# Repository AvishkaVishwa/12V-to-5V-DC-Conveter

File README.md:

# 12V to 5V DC Converter

## Overview
This project is a 12V to 5V DC-DC buck converter PCB design created with KiCad. The converter allows you to efficiently step down 12V DC power sources to 5V for powering various electronic devices and circuits.

## Features
- Input voltage: 12V DC
- Output voltage: 5V DC
- Buck converter topology for efficient power conversion
- Compact PCB design
- Ready for production

## Directory Structure
- `fabrication-toolkit-options.json` - Configuration for fabrication toolkit
- `PCB design Course.kicad_pcb` - KiCad PCB layout file
- `PCB design Course.kicad_sch` - KiCad schematic file
- `PCB design Course.kicad_pro` - KiCad project file
- `database/` - Project database files
- `PCB design Course-backups/` - Automatic backup files
- `production/` - Manufacturing files (Gerbers, BOM)

## Getting Started
1. Install [KiCad](https://www.kicad.org/download/)
2. Open `PCB design Course.kicad_pro` to view and modify the project
3. Use the schematic editor to view the circuit design
4. Use the PCB editor to view the board layout

## Manufacturing
The production directory contains all necessary files for manufacturing the PCB.

## License
This project is open-source hardware.

## Contributing
Contributions are welcome! Please feel free to submit a Pull Request.

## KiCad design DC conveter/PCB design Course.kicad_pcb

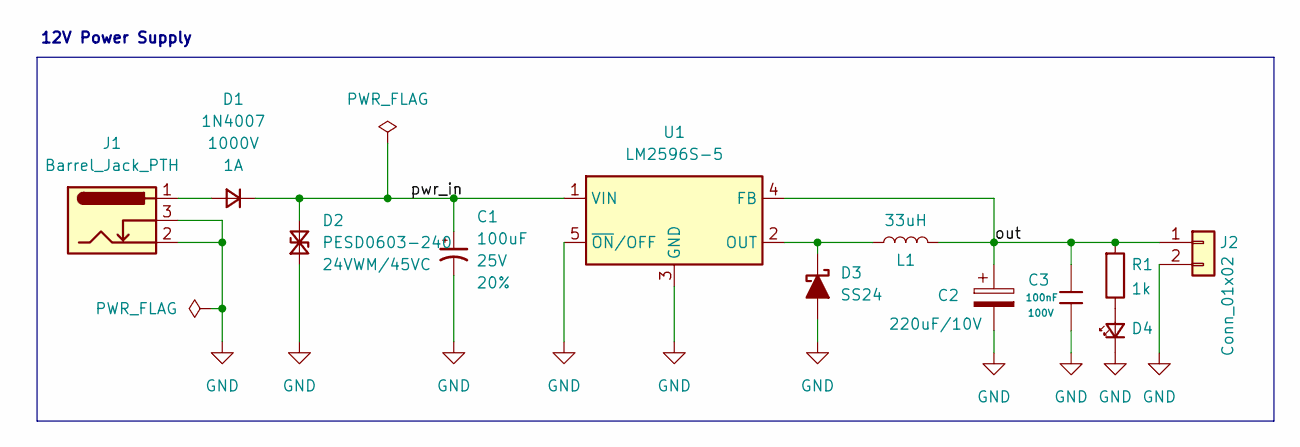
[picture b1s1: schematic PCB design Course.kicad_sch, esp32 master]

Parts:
C1: 100uF; CP_Elec_6.3x5.8; Voltage 25V; Tolerance 20%
C2: 220uF/10V; CP_Elec_6.3x5.4_Nichicon
C3: 100nF; C_0805; Voltage Rated 100V; Tolerance ±10%; Part CL21B104KCFNNNE; LCSC C28233
D1: 1N4007; D_DO-41_SOD81_P7.62mm_Horizontal
D2: PESD0603-240; D_DO-41_SOD81_P7.62mm_Horizontal; Rating 24VWM/45VC
D3: SS24; D_SMB
D4: Yellow; LED_0603_1608Metric_Yellow
J1: Barrel_Jack_PTH; BarrelJack_Horizontal
J2: Conn_01x02; TerminalBlock_MaiXu_MX126-5.0-02P_1x02_P5.00mm
L1: 33uH; L_12x12mm_H6mm
R1: 1k; R_0805_2012Metric
U1: LM2596S-5; TO-263-5_TabPin3

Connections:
/out: C2.1, C3.1, J2.1, L1.2, R1.1, U1.4 (FB)
/pwr_in: C1.1, D1.1 (K), D2.2 (A2), U1.1 (VIN)
GND: C1.2, C2.2, C3.2, D2.1 (A1), D3.2 (A), D4.1 (K), J1.2 (GND), J1.3 (GNDBREAK), J2.2, U1.3 (GND), U1.5 (~ON/OFF)
unnamed: D1.2 (A), J1.1 (PWR)
unnamed: D3.1 (K), L1.1, U1.2 (OUT)
unnamed: D4.2 (A), R1.2

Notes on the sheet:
12V Power Supply

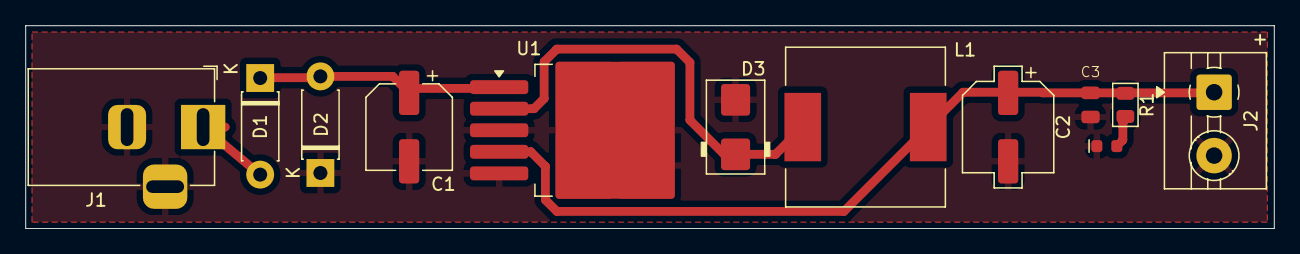
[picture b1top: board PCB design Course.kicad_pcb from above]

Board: 2 copper layers, 98.5 x 16.0 mm, 12 parts (0 on the bottom side), 6 nets.

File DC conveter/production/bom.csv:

Designator,Footprint,Quantity,Value,LCSC Part #
C1,CP_Radial_D5.0mm_P2.00mm,1,680uF/25V,
C2,CP_Elec_6.3x5.4_Nichicon,1,220uF/10V,
D2,D_SMB,1,SS24,
J1,BarrelJack_Horizontal,1,Barrel_Jack_PTH,
J2,PinHeader_1x02_P2.54mm_Vertical,1,Conn_01x02,
L1,L_12x12mm_H6mm,1,33uH,
U1,TO-263-5_TabPin3,1,LM2596S-5,

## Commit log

2025-04-14 Add initial project files including designators, BOM, netlist, and configuration
2025-04-14 Update README.md with project overview, features, directory structure, and getting started instructions
